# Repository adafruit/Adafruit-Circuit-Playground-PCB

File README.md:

## Adafruit Circuit Playground Classic PCB
<a href="http://www.adafruit.com/products/3000"><br/>
Click here to purchase one from the Adafruit shop</a>

This is the Classic version of Circuit Playground, which comes with an ATmega32u4. It's designed to be used with Arduino IDE and code.org CS Discoveries only. It even comes with Firmata already programmed in, so you can use it immediately with code.org Discoveries without any preparation or updates.

If you would like to use MakeCode or CircuitPython, check out [Circuit Playground Express](http://www.adafruit.com/products/3333), which can be used with MakeCode, CircuitPython or Arduino.

Circuit Playground features an ATmega32u4 processor, just like our popular Flora. The board's also round and has alligator-clip pads around it so you don't have to solder or sew to make it work. You can power it from USB, a AAA battery pack, or with a Lipoly battery (for advanced users). Just program your code into the board then take it on the go!

This is the PCB files for the Adafruit **Circuit Playground Classic** (not the Express). The format is EagleCAD schematic and board layout
- http://www.adafruit.com/products/3000

**The Circuit Playground Express can be found at http://www.adafruit.com/products/3333**

### License

Adafruit invests time and resources providing this open source design, please support Adafruit and open-source hardware by purchasing products from [Adafruit](https://www.adafruit.com)!

All text above must be included in any redistribution

Designed by Limor Fried/Ladyada for Adafruit Industries.
Creative Commons Attribution/Share-Alike, all text above must be included in any redistribution. 
See license.txt for additional information.

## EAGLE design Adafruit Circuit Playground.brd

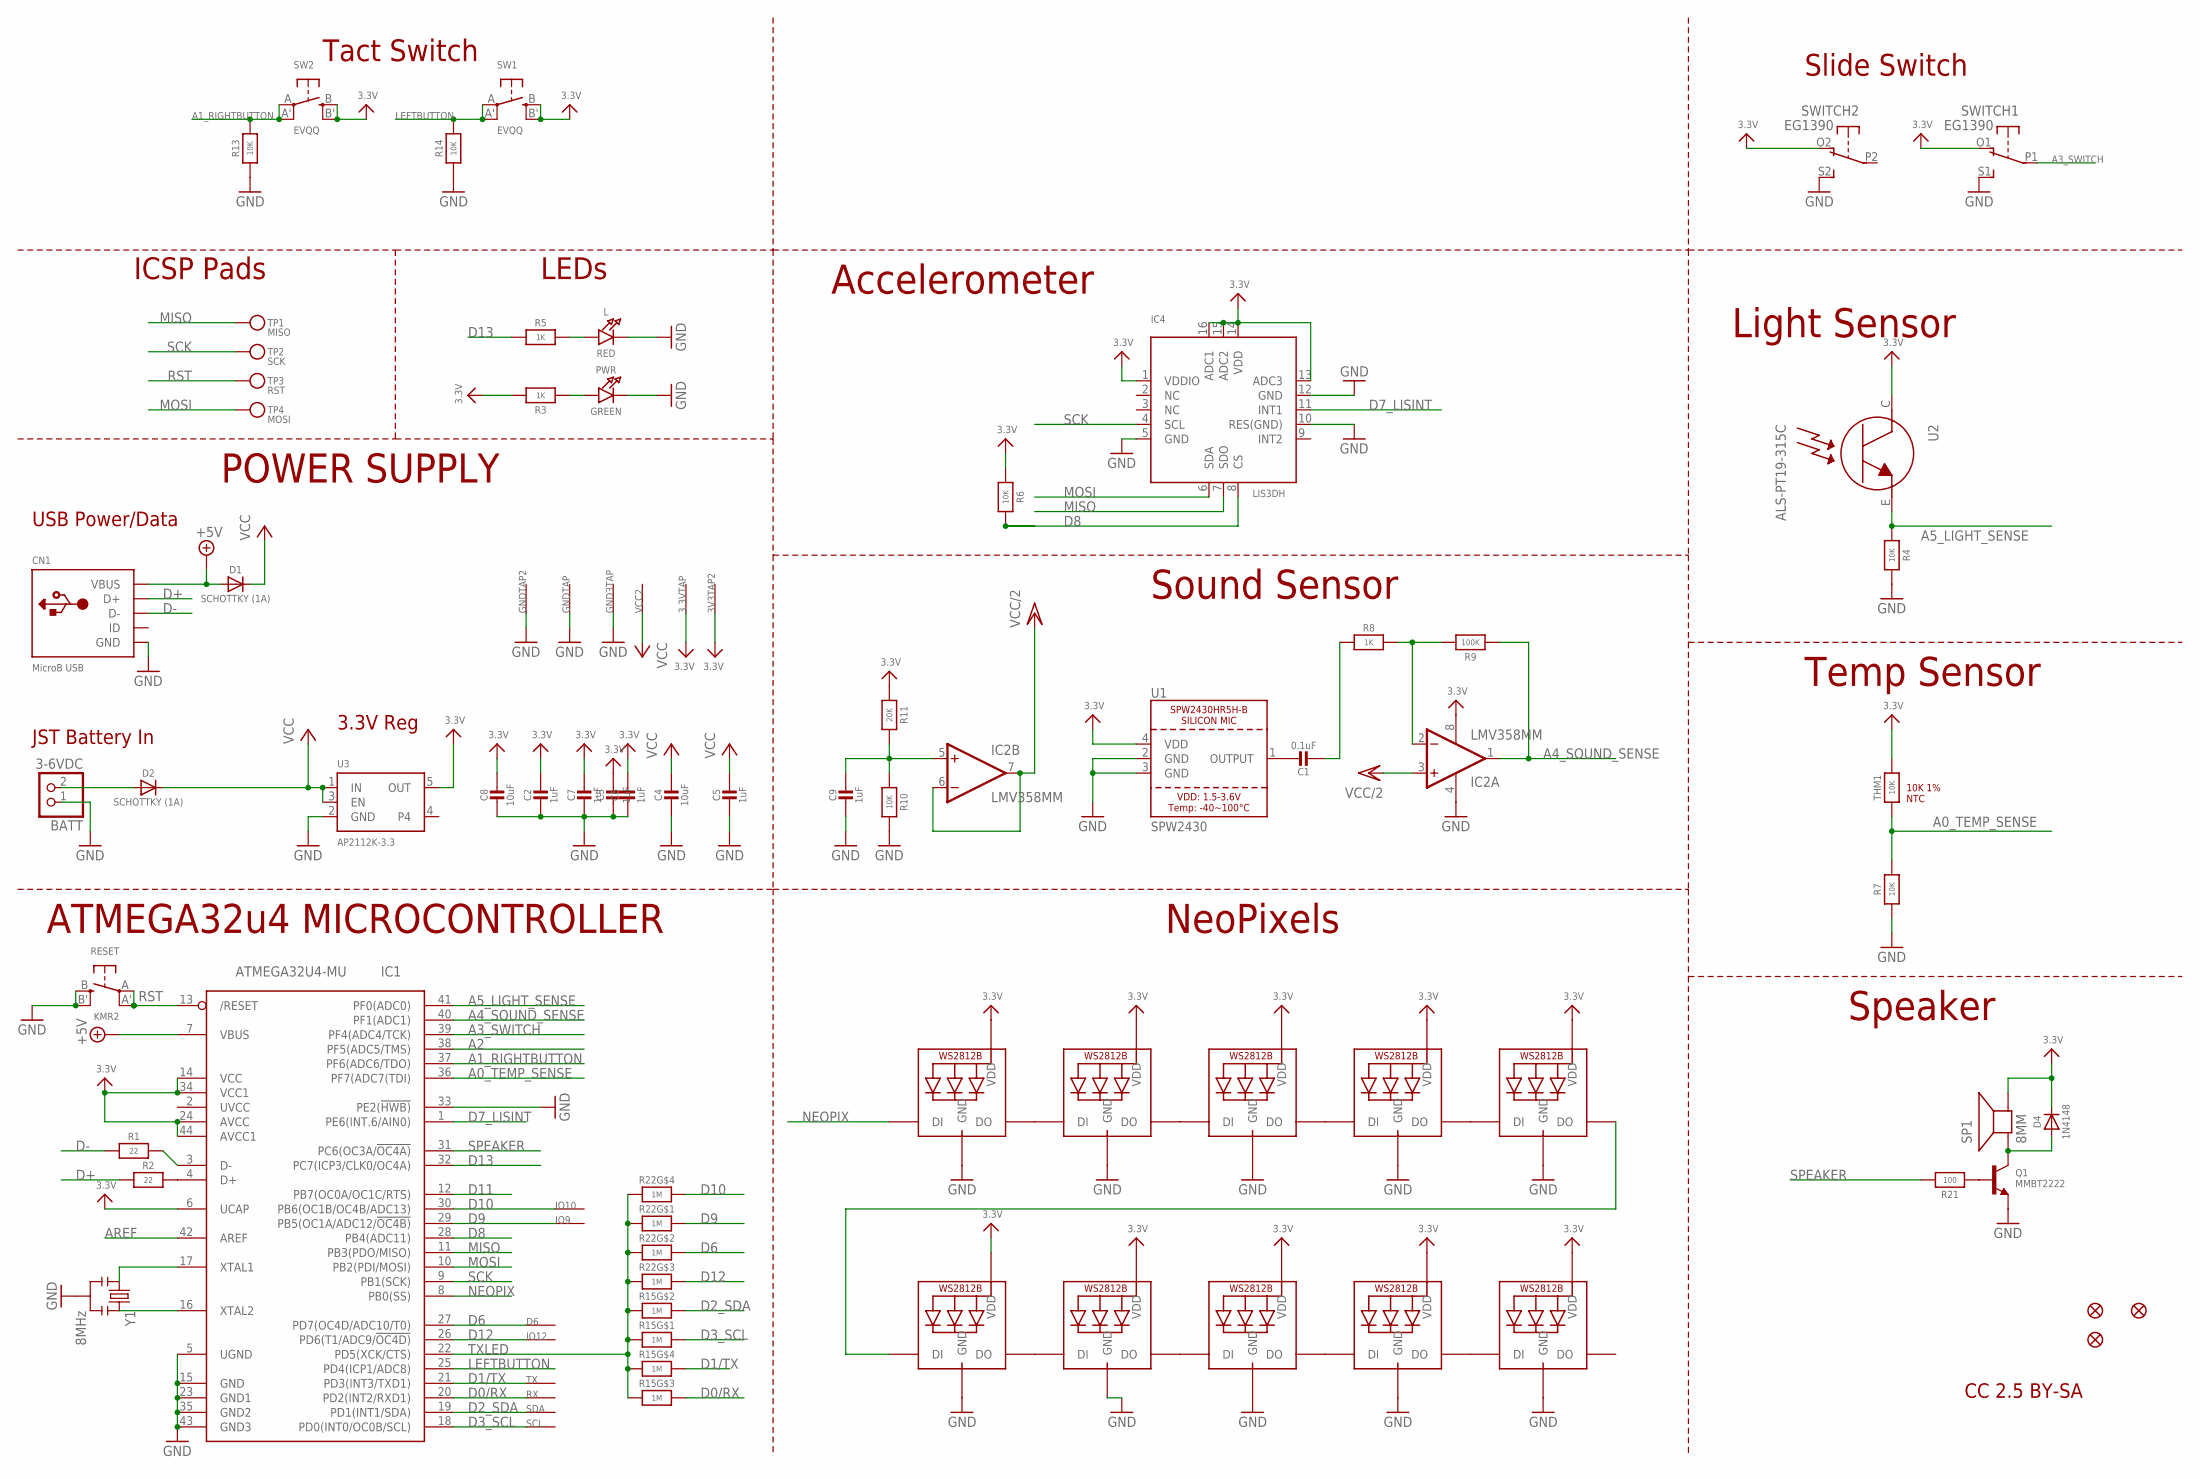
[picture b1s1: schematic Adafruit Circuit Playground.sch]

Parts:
3.3VTAP, 3V3TAP2: SEWTAP-ALLIGATOR; SEWALLI
BATT: 3-6VDC; JSTPH2
C1: 0.1uF; 0603-NO
C2, C3, C5, C6, C7, C9: 1uF; 0603-NO
C4, C8: 10uF; 0805-NO
CN1: MicroB USB; 4UCONN_20329_V2
D1, D2: SCHOTTKY (1A); SOD-123
D4: 1N4148; SOD-323
D6: SEWTAP-ALLIGATOR; SEWALLI
GND3TAP: SEWTAP-ALLIGATOR; SEWALLI
GNDTAP, GNDTAP2: SEWTAP-ALLIGATOR; SEWALLI
IC1: ATMEGA32U4-MU; TQFN44_7MM
IC2: LMV358MM; MSOP08
IC4: LIS3DH; LGA16_3X3MM
IO9, IO10, IO12: SEWTAP-ALLIGATOR; SEWALLI
L: RED; CHIPLED_0805_NOOUTLINE
LED1, LED2, LED3, LED4, LED5, LED6, LED7, LED8, LED9, LED10: WS2812B3535; LED3535
PWR: GREEN; CHIPLED_0805_NOOUTLINE
Q1: MMBT2222; SOT23-WIDE
R1, R2: 22; 0603-NO
R3, R5, R8: 1K; 0603-NO
R4, R6, R7, R10, R13, R14: 10K; 0603-NO
R9: 100K; 0603-NO
R11: 20K; 0603-NO
R15, R22: 1M; RESPACK_4X0603_NO
R21: 100; 0603-NO
RESET: KMR2; BTN_KMR2_4.6X2.8
RX: SEWTAP-ALLIGATOR; SEWALLI
SCL: SEWTAP-ALLIGATOR; SEWALLI
SDA: SEWTAP-ALLIGATOR; SEWALLI
SP1: 8MM; BUZZER_SMT_5MM
SW1, SW2: EVQQ; EVQ-Q2_SMALLER
SWITCH: EG1390
THM1: 10K; _0402
TP1: MISO; TESTPOINT_ROUND_1.5MM
TP2: SCK; TESTPOINT_ROUND_1.5MM
TP3: RST; TESTPOINT_ROUND_1.5MM
TP4: MOSI; TESTPOINT_ROUND_1.5MM
TX: SEWTAP-ALLIGATOR; SEWALLI
U1: SPW2430; SPW2430HR5H-B
U2: ALS-PT19-315C
U3: AP2112K-3.3; SOT23-5
U$2, U$3, U$6: FIDUCIAL""; FIDUCIAL_1MM
VCC2: SEWTAP-ALLIGATOR; SEWALLI
Y1: 8MHz; RESONATOR-SMD

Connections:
3.3V: 3.3VTAP.P$1, 3V3TAP2.P$1, C2.1, C3.1, C6.1, C7.1, C8.1, D4.C, IC1.6 (UCAP), IC1.14 (VCC), IC1.24 (AVCC), IC1.34 (VCC1), IC1.44 (AVCC1), IC2.8 (V+), IC4.1 (VDDIO), IC4.13 (ADC3), IC4.14 (VDD), IC4.15 (ADC2), IC4.16 (ADC1), LED1.2 (VDD), LED2.2 (VDD), LED3.2 (VDD), LED4.2 (VDD), LED5.2 (VDD), LED6.2 (VDD), LED7.2 (VDD), LED8.2 (VDD), LED9.2 (VDD), LED10.2 (VDD), R3.2, R6.1, R11.1, SP1.-, SW1.B (S), SW1.B' (S1), SW2.B (S), SW2.B' (S1), SWITCH.O1 (O), SWITCH.O2 (O), THM1.2, U1.4 (VDD), U2.C, U3.5 (OUT)
+5V: CN1.VBUS, D1.A, IC1.7 (VBUS)
A0_TEMP_SENSE: IC1.36 (PF7(ADC7(TDI)), R7.2, THM1.1
A1_RIGHTBUTTON: IC1.37 (PF6(ADC6/TDO)), R13.2, SW2.A, SW2.A' (P1)
A2: IC1.38 (PF5(ADC5/TMS))
A3_SWITCH: IC1.39 (PF4(ADC4/TCK)), SWITCH.P1
A4_SOUND_SENSE: IC1.40 (PF1(ADC1)), IC2.1 (OUT), R9.1
A5_LIGHT_SENSE: IC1.41 (PF0(ADC0)), R4.2, U2.E
AREF: IC1.42 (AREF)
D0/RX: IC1.20 (PD2(INT2/RXD1)), R15.6 (2), RX.P$1
D1/TX: IC1.21 (PD3(INT3/TXD1)), R15.5 (2), TX.P$1
D2_SDA: IC1.19 (PD1(INT1/SDA)), R15.7 (2), SDA.P$1
D3_SCL: IC1.18 (PD0(INT0/OC0B/SCL)), R15.8 (2), SCL.P$1
D6: D6.P$1, IC1.27 (PD7(OC4D/ADC10/T0)), R22.7 (2)
D7_LISINT: IC1.1 (PE6(INT.6/AIN0)), IC4.11 (INT1)
D8: IC1.28 (PB4(ADC11)), IC4.8 (CS), R6.2
D9: IC1.29 (PB5(OC1A/ADC12/!OC4B)), IO9.P$1, R22.8 (2)
D10: IC1.30 (PB6(OC1B/OC4B/ADC13)), IO10.P$1, R22.5 (2)
D11: IC1.12 (PB7(OC0A/OC1C/RTS))
D12: IC1.26 (PD6(T1/ADC9/!OC4D)), IO12.P$1, R22.6 (2)
D13: IC1.32 (PC7(ICP3/CLK0/OC4A)), R5.1
D+: CN1.D+, R2.1
D-: CN1.D-, R1.1
GND: BATT.1, C2.2, C3.2, C4.2, C5.2, C6.2, C7.2, C8.2, C9.2, CN1.BASE@1 (GND), CN1.BASE@2 (GND), CN1.GND, CN1.SPRT@1 (GND), CN1.SPRT@2 (GND), CN1.SPRT@3 (GND), CN1.SPRT@4 (GND), GND3TAP.P$1, GNDTAP.P$1, GNDTAP2.P$1, IC1.5 (UGND), IC1.15 (GND), IC1.23 (GND1), IC1.33 (PE2(!HWB)), IC1.35 (GND2), IC1.43 (GND3), IC2.4 (V-), IC4.5 (GND), IC4.10 (RES(GND)), IC4.12 (GND), L.C, LED1.4 (GND), LED2.4 (GND), LED3.4 (GND), LED4.4 (GND), LED5.4 (GND), LED6.4 (GND), LED7.4 (GND), LED8.4 (GND), LED9.4 (GND), LED10.4 (GND), PWR.C, Q1.2 (E), R4.1, R7.1, R10.2, R13.1, R14.1, RESET.B (S), RESET.B' (S1), SWITCH.S1 (S), SWITCH.S2 (S), U1.2 (GND), U1.3 (GND), U3.2 (GND), Y1.2
LEFTBUTTON: IC1.25 (PD4(ICP1/ADC8)), R14.2, SW1.A, SW1.A' (P1)
MISO: IC1.11 (PB3(PDO/MISO)), IC4.7 (SDO), TP1.P$1
MOSI: IC1.10 (PB2(PDI/MOSI)), IC4.6 (SDA), TP4.P$1
unnamed: PWR.A, R3.1
unnamed: IC2.2 (-IN), R8.2, R9.2
unnamed: IC1.3 (D-), R1.2
unnamed: IC1.4 (D+), R2.2
unnamed: C9.1, IC2.5 (+IN), R10.1, R11.2
unnamed: BATT.2, D2.A
unnamed: IC1.17 (XTAL1), Y1.1
unnamed: IC1.16 (XTAL2), Y1.3
unnamed: L.A, R5.2
unnamed: LED1.1 (DI), LED2.3 (DO)
unnamed: LED1.3 (DO), LED3.1 (DI)
unnamed: LED2.1 (DI), LED10.3 (DO)
unnamed: LED6.3 (DO), LED7.1 (DI)
unnamed: C1.2, R8.1
unnamed: LED7.3 (DO), LED8.1 (DI)
unnamed: LED8.3 (DO), LED9.1 (DI)
unnamed: LED9.3 (DO), LED10.1 (DI)
unnamed: LED3.3 (DO), LED4.1 (DI)
unnamed: LED4.3 (DO), LED5.1 (DI)
unnamed: D4.A, Q1.3 (C), SP1.+
unnamed: Q1.1 (B), R21.1
NEOPIX: IC1.8 (PB0(SS)), LED6.1 (DI)
RST: IC1.13 (/RESET), RESET.A, RESET.A' (P1), TP3.P$1
SCK: IC1.9 (PB1(SCK)), IC4.4 (SCL), TP2.P$1
SOUNDOUT: C1.1, U1.1 (OUTPUT)
SPEAKER: IC1.31 (PC6(OC3A/!OC4A)), R21.2
TXLED: IC1.22 (PD5(XCK/CTS)), R15.1, R15.2 (1), R15.3 (1), R15.4 (1), R22.1, R22.2 (1), R22.3 (1), R22.4 (1)
VCC: C4.1, C5.1, D1.C, D2.C, U3.1 (IN), U3.3 (EN), VCC2.P$1
VCC/2: IC2.3 (+IN), IC2.6 (-IN), IC2.7 (OUT)

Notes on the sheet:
CC 2.5 BY-SA
10K 1% NTC
ATMEGA32u4 MICROCONTROLLER
USB Power/Data
JST Battery In
3.3V Reg
POWER SUPPLY
NeoPixels
Speaker
Temp Sensor
Light Sensor
Sound Sensor
Slide Switch
Tact Switch
LEDs
ICSP Pads
Accelerometer

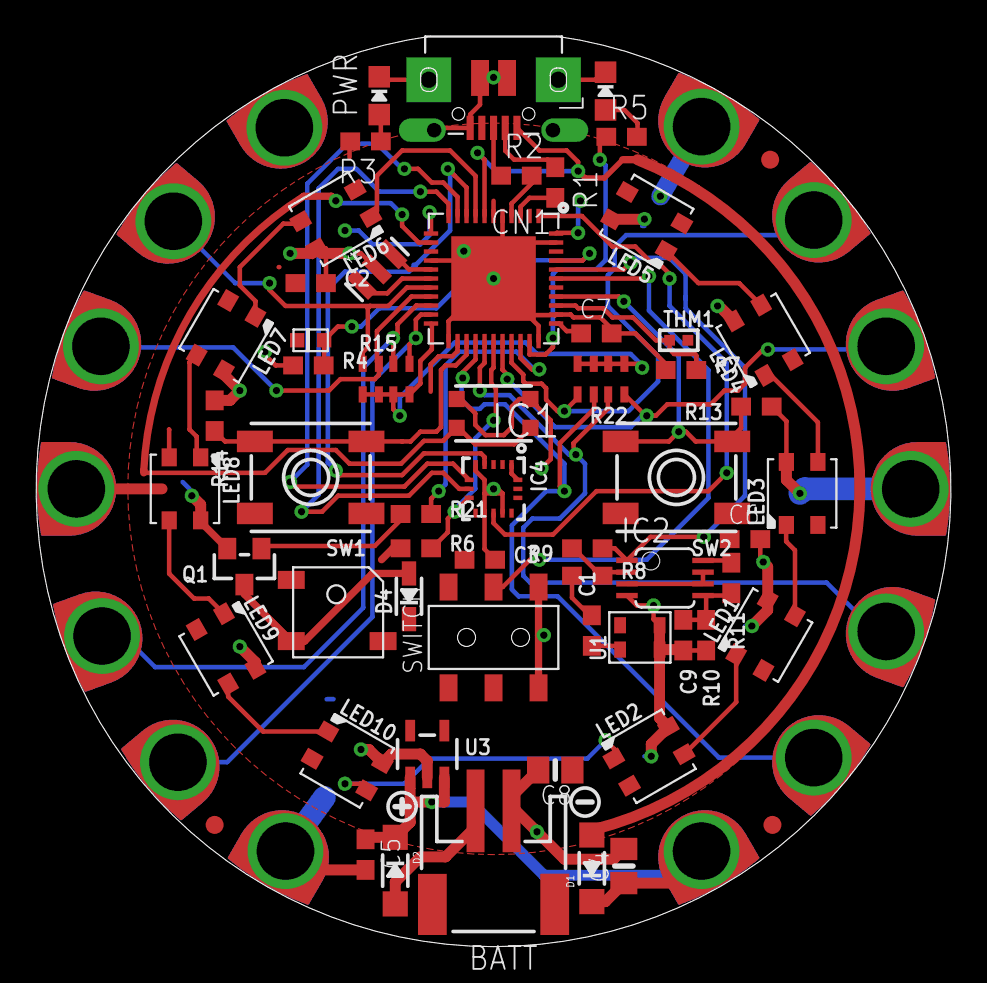
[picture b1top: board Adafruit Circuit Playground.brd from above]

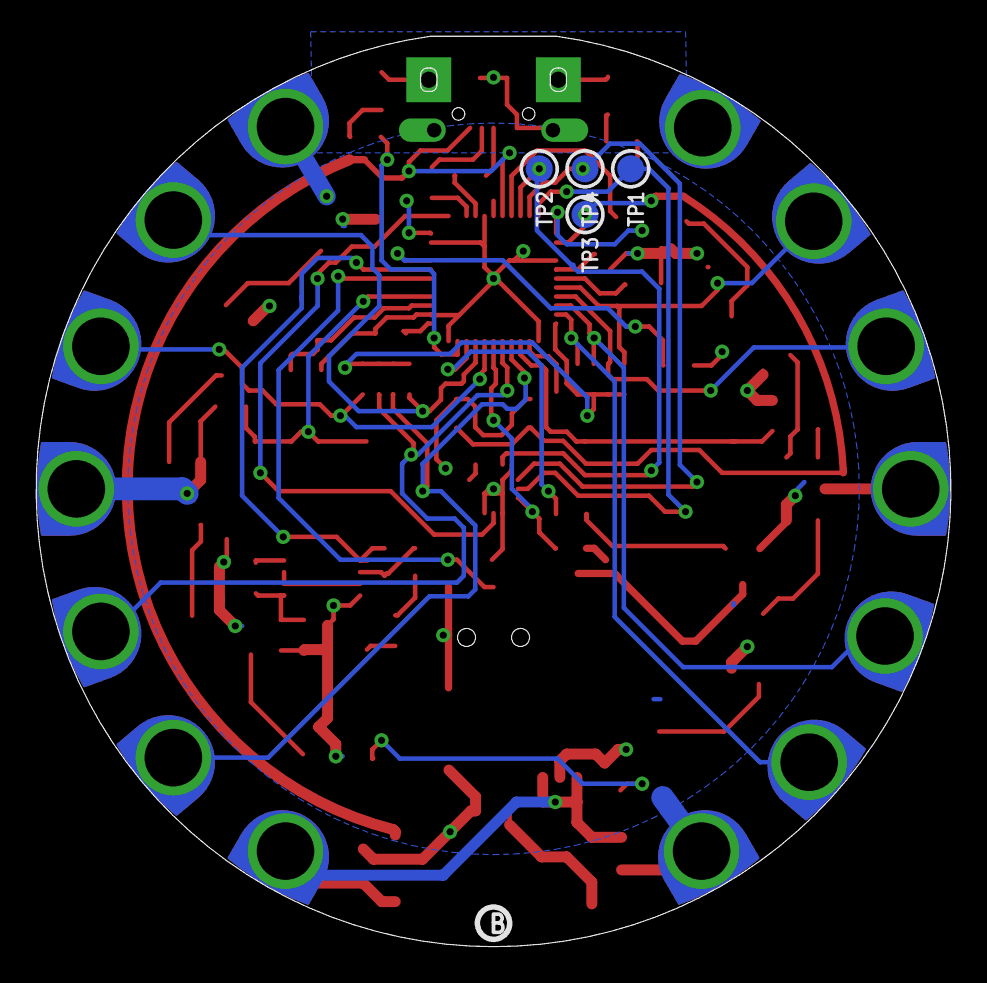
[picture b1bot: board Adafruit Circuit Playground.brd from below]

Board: 2 copper layers, 50.8 x 50.6 mm, 83 parts (7 on the bottom side), 53 nets.

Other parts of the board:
U$1: SYMBOL_MINUS
U$4: FLORAMED
U$7: PCBFEAT-REV-040
U$34: CPLAYFRONT
U$35: SYMBOL_PLUS
U$46: CPLAYBACK

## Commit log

2016-04-26 init

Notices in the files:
parts and their libraries:
microbuilder: This work is placed in the public domain, and may be freely used for commercial and non-commercial work with the following conditions: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
SparkFun: Licensing: CC v3.0 Share-Alike You are welcome to use this library for commercial purposes.
